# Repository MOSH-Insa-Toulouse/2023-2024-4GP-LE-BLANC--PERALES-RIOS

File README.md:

# Graphite-based sensor project

## Students: Maël LE BLANC, Daniel PERALES RIOS

Département de Génie Physique

Institut National des Sciences Appliquées de Toulouse

# Introduction
The aim of this project is to study a graphite-based low-tech sensor, based on the publication "Pencil Drawn Strain Gauges and Chemiresistors on Paper" by Cheng-Wei Lin, Zhibo Zhao, Jaemyung Kim & Jiaxing Huang, published on Nature in 2014.

According to this research, graphite particles, deposited by coloring a sensor trace, can act as strain gauges. These strain gauges can then be used to measure resistances of the order of the Giga-ohm (10E9 Ohms), for a much cheaper price than buying a multimeter able to measure this order of resistance.

To study this graphene-based low-tech sensor, we have made an amplifier circuit that allows to measure the current flowing through the graphite sensor. This current is very small, and to measure it we would need a very expensive multimeter. Moreover, as the resistance of the graphene sensor depends on each graphite sensor, we have added a digital potentiometer in one of the resistances of the amplifier circuit. This allows for tuning the circuit to each sensor. We have also added a flex sensor to the project. The resistance of this sensor depends on the bending angle applied to it.

All the sensors and measurements are managed through an Arduino UNO board. In this Arduino UNO board, we have also connected an OLED screen that displays the data being measured. We have also implemented a simple menu in the screen that can be controlled through a rotary encoder. All the gathered data is then sent via a Bluetooth® module to an Android device though an app we have built using MIT’s App Inventor.

Finally, we have mounted all the sensors in a PCB we have built from scratch using KiCAD v7.0.

This project covers the entire sensor field, right up to the development of a datasheet and test bench for this sensor.

- [Deliverables](#deliverables)

- [Physics behind the resistance change in the graphite and the flex sensors](#physics-behind-the-resistance-change-in-the-graphite-and-the-flex-sensors)

- [Necessary components and image of the finished project](#necessary-components-and-image-of-the-finished-project)

- [Arduino code](#arduino-code)
  
    - [Potentiometer menu](#potentiometer-menu)
    - [Flex sensor menu](#flex-sensor-menu)
    - [Graphite sensor menu](#graphite-sensor-menu)

- [KiCAD PCB design](#kicad-pcb-design)

    - [Amplifier circuit](#amplifier-circuit)
    - [LTC1050 Operationnal amplifier](#ltc1050-operationnal-amplifier)
    - [MCP41050 Digital potentiometer](#mcp41050-digital-potentiometer)
    - [Graphite sensor](#graphite-sensor)
    - [Flex sensor](#flex-sensor)
    - [KY-040 Rotary encoder](#ky-040-rotary-encoder)
    - [OLED screen](#oled-screen)

- [Android App](#android-app)

- [Test Bench](#test-bench)

# Deliverables

- Arduino shield containing the BT module, the OLED screen...
- Arduino code for controlling the Arduino shield.
- Android app that is able to gather the data sent by the Arduino shield.
- Datasheet describing the results of some measurements for the sensors. 

To write the datasheet, a bench test must be used or built. In our project, we have used a bench test that was already at the department, and that was perfect for our case.

# Physics behind the resistance change in the graphite and the flex sensors

For the graphite and the flex sensors, let’s imagine they were a 2D layer of atoms to which we could apply tension and compression. This 2D layer of atoms would have a mean distance per atom depending on the atomic arrangement. The greater these mean distance between atoms is, the more difficult it is for an electron to “jump” from one atom to another, and vice versa. When these electron “jumps” are coordinated following the same direction (for example when we apply a potential difference between the two extremes of the 2D plane), we can say that an electric current is present. When this happens, it is called "percolation".

On the one hand, when a compression force is applied to that 2D layer of atoms, the atoms would get closer to each other, thus reducing the mean distance per atom, facilitating the flow of an electric current, and reducing then the resistance. 

On the other hand, when a tensile force is applied to the 2D layer of atoms, the atoms would get farther apart from each other, thus increasing the mean distance per atom, making the electron “jumps” less favorable, and increasing the resistance. 

We can see in figure 1 how the compressive and tensile forces affect the geometry of the 2D plane. When generalizing the 2D plane to a 3D thin surface, the principle of the measurement stays the same.

Figure 1: Principle of the resistance measurement for the graphite and flex sensors. Extracted from “Pencil Drawn Strain Gauges and Chemiresistors on Paper”, by Cheng-Wei et al.

# Necessary components and image of the finished project

In figure 2, the finished project, with all the components mounted on the shield, is showed. The only component that not mounted in the shield has been the Bluetooth module, since what we thought to be a connection error was blocking the Arduino code from running.

To carry out this project, we needed: 
  - 1 graphite-based paper sensor
  - 1 flex sensor
  - 1 LTC1050 operational amplifier
  - 1 MCP41050 digital potentiometer
  - 1 KY-040 rotary encoder
  - 1 Arduino UNO
  - 1 OLED screen
  - 1 HC-05 Bluetooth® module
  - Resistances
  - Capacitors

Figure 2: Image of the complete project. The Bluetooth module is mounted on a separate Arduino breadboard, but this does not have any impact on the functioning of the program.

# Arduino code

The logic behind the Arduino program can be found in the logic chart in figure 3.

Figure 3: Logic chart for the Arduino code, that shows what are the main procedures and methods and what the code mainly does.

The is a main menu with three options, and the user can choose between each of these three options: the potentiometer, the flex sensor and the graphite sensor. These menus are showed below.

## Potentiometer menu

In this menu, the user selects the resistance value to be given to the potentiometer by placing the cursor over the available values. The user exits the calibration menu by pressing the encoder button. 

Figure 4: Potentiometer menu.

## Flex sensor menu

In this menu, the value of the resistance and the value of the angle of the flex sensor are displayed.  

Figure 5: Flex sensor menu.

## Grpahite sensor menu

In this menu, the user can see the current value of the graphite sensor. The user exits to the main menu by pressing the encoder button.

Figure 6: Graphite sensor menu.

# KiCAD PCB design

To realise our PCB, we have used KiCAD under its 7.0 version.

First of all, we had to reproduce the electrical amplifier circuit (resistances, capacitors...) with a few changes and component additions. In order to adjust the gain of our circuit, we have replaced the resistance R2 by an MCP41050 digital potentiometer which can be controlled using the KY-040 rotary encoder. Then, for the realisation of the test bench, we had to add some components that need to be connected to the power source, such as the flex sensor, the Bluetooth® module or the OLED screen. For that, we have created some symbols associated to the new elements. 

On figure 7, it is possible to see our complete electrical circuit realised in KiCAD with the different symbols of the components. 

Figure 7 : Complete schematic of the electrical circuit in KiCAD for the project.

Then, the second part is to realise the footprint of the PCB on KiCAD. However, all the components and the whole circuit have to fit on Arduino Uno Shield. So, the spatial arrangement must be thoughtful, while considering the 3D shape of the components and the specifications we have to follow for the PCB printing. 

For the most commons components, we've used some predefined footprints but for the others we've created some specifical footprints thanks to the software. All the footprints can be found in the KiCAD folder.

## Amplifier circuit

The main role of the amplifier is to amplify sensor output voltages to make them measurable.

On figure 8 can be seen the electrical circuit of the amplifier.

Figure 8: Schematic of the operationnal amplifier circuit in KiCAD.

## LTC1050 Operationnal amplifier

The LTC1050 is the operationnal amplifier used in our amplifier circuit that can be observed in figure 9.

Figure 9: LTC1050 operational amplifier.

## MCP41050 Digital potentiometer

The MCP41050 is the digital potentiometer used in our project. It varies up to 50,000 ohms depending on the command sent.
It has eight connections pins as can be seen in figure 10. 

Figure 10: MCP41050 digital potentiometer.

## Graphite sensor

The graphite sensor used in our project is made from paper with a trace to be colored in with different pencils. 
In our electrical circuit, the sensor is connected between the 5V (Vcc) source and the positive input of the amplifier (Vout), as can be seen in figure 11.

Figure 11: Schematic for the graphite sensor. Extracted from Niels Brun and Paul Besnard's GitHub site.

## Flex sensor

The flex sensor, used for comparing the graphite-sensor measures, is mounted in a voltage divider bridge. 

Figure 12: Flex sensor. 

## KY-040 Rotary encoder

The rotary encoder is a main part of our project. It allows the user to change the selected menu, enter and exit menus by turning or pressing the encoder.
The rotary encoder has five pins connected to differents parts of the shield, as you can see on figure 13.  

Figure 13: Rotary encoder KY-040.

## OLED screen

On the Arduino shield, the OLED screen is connected to four pins, as you can see on figure 14.

Figure 14: The OLED screen, with four pins.

# Android app

The Android app has been coded using MIT's app inventor. In figure 15 can be seen a logic chart for the functioning of the app.

Figure 15: Logic chart for the Android app.

In figure 16 can be seen the code blocks for the Android app. 

Figure 16: Code blocks for the Android app. 

Moreover, we have coded an improved version of the program with a login function, whose code appears in figure 17.

Figure 17: Code blocks for the Android app with the login function.

Next, in figures 18 and 19 are presented the data capture screen and the login screen, respectively.

Figure 18: Data capture screen.

Figure 19: Login screen.

# Test bench

The last part of our project was to realize the test bench to acquire the data from our sensors. 

To realize the measures, we have decided to use a test bench consisting of semi-cylinders going from 2 to 5 cm in diameter, with steps of 0.5 cm in between each semi-cylinder, as you can see on figure 20.

Figure 20: Test bench used.

We have tested 5 graphite-sensors. Each, made with a different type of pencil: 3B, 2B, B, H, 2H. 
To carry out the measurements, we placed the sensors on the various cylinders, in tension and compression, as can be seen respectively in figures 21 and 22. This enabled us to measure differences in resistance as a function of pencil type and deformation. 

Figure 21: Deformation in tension.

Figure 22: Deformation in compression.

In figure 23 the results for the flex sensor in tension are showed. 

Figure 23: Results for the flex sensor, in tension.

The complete results are described and presented in the graphite sensors' datasheet, available in the Datasheet folder.

With our results it is found that the softer the pencil is (in our case, 3B is the softer pencil), the less sensitive it is. This is the same conclusion, saving the distance, of Wei et al. in “Pencil Drawn Strain Gauges and Chemiresistors on Paper”.

For any question concerning our sensor project, please contact: perales@insa-toulouse.fr / m_leblan@insa-toulouse.fr

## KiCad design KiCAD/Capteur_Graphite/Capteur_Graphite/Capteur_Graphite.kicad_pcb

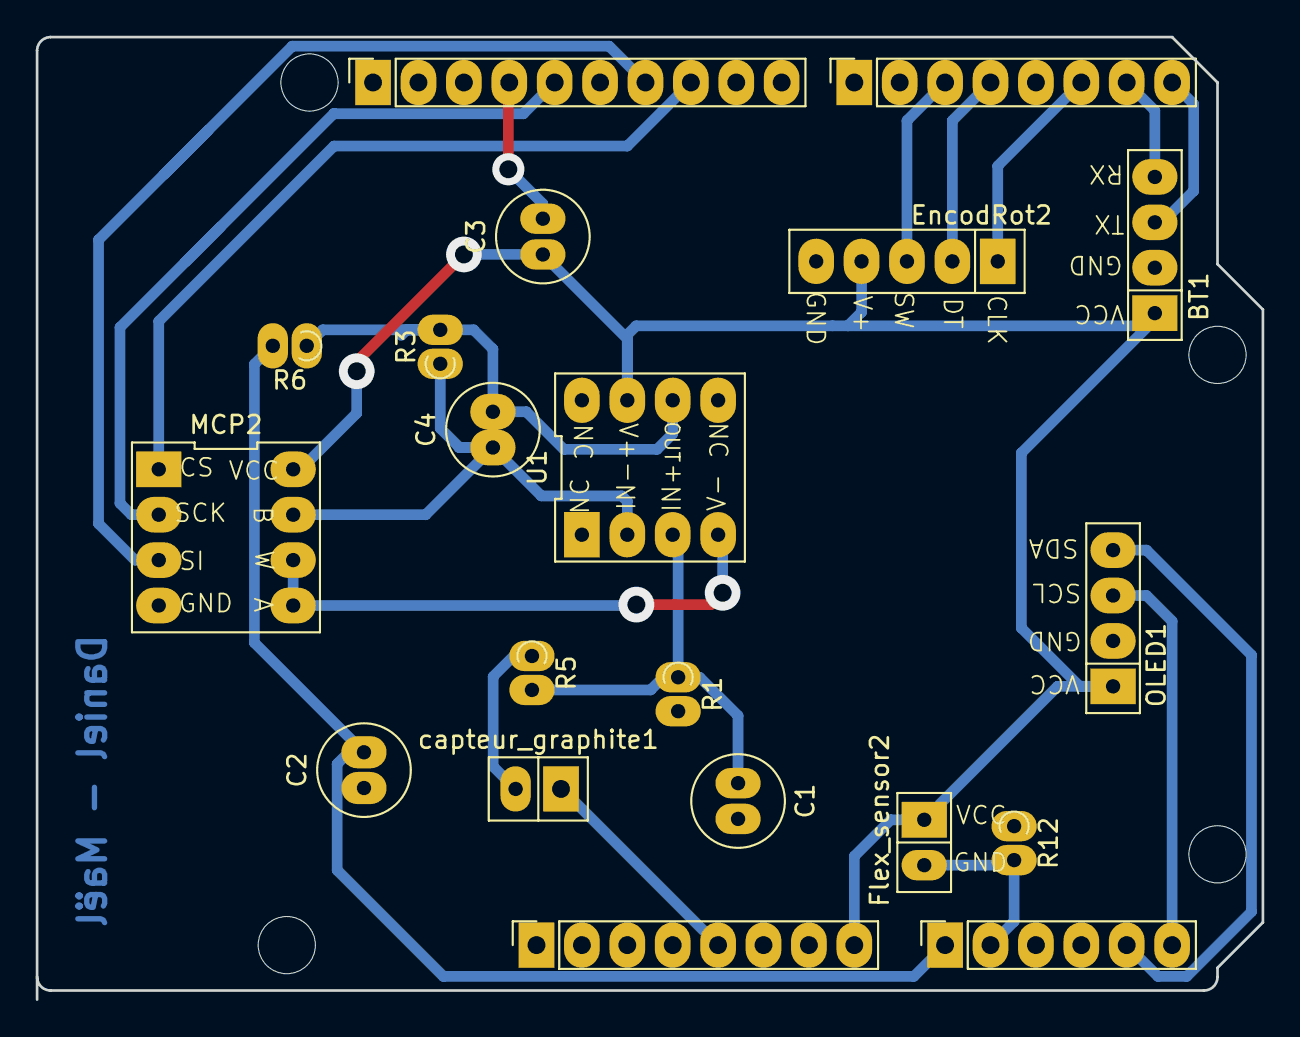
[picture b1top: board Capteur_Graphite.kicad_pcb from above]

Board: 2 copper layers, 68.6 x 53.8 mm, 24 parts (0 on the bottom side), 18 nets.

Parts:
BT1: Bluetooth
C1, C3: 100N; C_Radial_D5.0mm_H5.0mm_P2.00mm
C2: 100n; C_Radial_D5.0mm_H5.0mm_P2.00mm
C4: 1u; C_Radial_D5.0mm_H5.0mm_P2.00mm
EncodRot2: Encodeur
Flex_sensor2: FLEX
J1: Power; PinSocket_1x08_P2.54mm_Vertical
J2: Digital/PWM; PinSocket_1x10_P2.54mm_Vertical
J3: Analog; PinSocket_1x06_P2.54mm_Vertical
J4: Digital/PWM; PinSocket_1x08_P2.54mm_Vertical
MCP2: MCP41050
MH1, MH2, MH3, MH4: MountingHole_3.2mm
OLED1: OLED
R1: 100K; R_Axial_DIN0204_L3.6mm_D1.6mm_P1.90mm_Vertical
R3: 100k; R_Axial_DIN0204_L3.6mm_D1.6mm_P1.90mm_Vertical
R5: 10k; R_Axial_DIN0204_L3.6mm_D1.6mm_P1.90mm_Vertical
R6: 1k; R_Axial_DIN0204_L3.6mm_D1.6mm_P1.90mm_Vertical
R12: 56.4K; R_Axial_DIN0204_L3.6mm_D1.6mm_P1.90mm_Vertical
U1: LTC1050
capteur_graphite1: Capteur_graphite

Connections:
A0: C2.2, J3.1, R6.2
A1: Flex_sensor2.2 (GND), J3.2, R12.2
D2: EncodRot2.1 (CLK), J4.6
D4: EncodRot2.2 (DT), J4.4
D5: EncodRot2.3 (SW), J4.3
GND: BT1.2 (GND), C1.2, C2.1, C3.2, EncodRot2.5 (GND), J1.6, J1.7, J2.4, MCP2.4 (GND), MCP2.5 (A), MCP2.6 (W), OLED1.2 (GND), R1.2, R12.1, U1.4 (V-)
unnamed: C4.2, R3.2, R6.1, U1.6
unnamed: C4.1, MCP2.7 (B), R3.1, U1.2 (-)
unnamed: C1.1, R1.1, R5.2, U1.3 (+)
unnamed: R5.1, capteur_graphite1.2 (SENSE)
RX: BT1.3 (TX), J4.8
SCK: J2.5, MCP2.2 (SCK)
SCL/A5: J2.1, J3.6, OLED1.3 (SCL)
SDA/A4: J2.2, J3.5, OLED1.4 (SDA)
SI: J2.7, MCP2.3 (SI)
SS: J2.8, MCP2.1 (CS)
TX: BT1.4 (RX), J4.7
Vcc: BT1.1 (Vcc), C3.1, EncodRot2.4 (V+), Flex_sensor2.1 (Vcc), J1.5, J1.8, MCP2.8 (VCC), OLED1.1 (VCC), U1.7 (V+), capteur_graphite1.1 (VCC)

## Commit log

2024-04-05 Add files via upload
    Uploading all the previous files
2024-04-05 Update Code_complet.ino
    Updating the BT branch
2024-04-05 Miscellaneous files
    .
2024-04-20 Update README.md
    update PCB
2024-05-29 Delete KiCAD/KiCADv6 directory
    fock
2024-05-29 add kicad file
    kicad
2024-05-29 Update README.md
    ampli
2024-05-29 Update README.md
    kicad part in readme without images
2024-05-29 Update README.md
    komit
    caumitte
    khaumythe
2024-06-04 Update Code_complet.ino
    Indenting some comments
2024-06-04 Update Code_complet.ino
    Indenting some comments.
2024-06-04 Add files via upload
    Android program added
2024-06-04 Add files via upload
    Added Android app with login function
2024-06-04 Add files via upload
    Added bench test
2024-06-04 Add files via upload
    Added the logo for the app
2024-06-04 Add files via upload
    Added all the KiCAD files and the 3D models
2024-06-04 Add files via upload
    Added the oral presentation (FR)
2024-06-05 Add files via upload
    Added description for the logo
2024-06-05 Added .aia files
2024-06-05 Results
2024-06-05 Updated datasheet
2024-06-05 Last update README.md
